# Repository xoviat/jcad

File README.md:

# JCAD: A JLCPCB Manufacturing File Generator for KiCad

JCAD is a program to generate manufacturing files for JLCPCB directly from a `.kicad_pcb` file.
In contrast to other approaches, JCAD does not integrate with KiCad directly or require modification
of schematic or PCB design files in order to generate outputs. Instead, JCAD relies on a consistent
component naming scheme that allows the program to generate manufacturing files from a PCB file in
seconds once the configuration has been established.

## How JCAD works

JCAD associates each combination of designator, footprint, and value on a KiCad PCB with a specific
JLCPCB part. JCAD uses KiCad's new builtin command line client to extract data from the KiCad files
then matches this data with its internal database to prepare manufacturing files.

To reduce designer configuration, JCAD relies on a strict naming scheme for basic parts, and a more
flexible naming scheme for extended parts:

- Basic capacitors, inductors, and resistors must be named unitless
    * Example: 10u, 10k, 10p
- Numerical component values must be equal to or greater than 1, and must use decimal format
    * Example: 10.1k, 10.5p
- Designators must be labeled as follows:
    * Inductors, ferrite beads, and common-mode chokes must be labeled with the L designator
    * Transformers must be labeled with the T designator
    * Crystals must be labeled with the Y designator
- Extended components, including capacitors, inductors, and resistors, and all other basic components must be given the manufacturer name

## Generating Manufacturing Files

The core of JCAD is the `jcad generate` command. The command, when executed in the directory of a `.kicad_pcb` file, reads the PCB and generates three files:
- A `.zip` file containing the gerbers that can uploaded on the order page
- The `-cpl.csv` and `-BOM.csv` files that can be uploaded on the assembly page

If only basic parts are used, and if naming conventions are adhered to, then no
additional user input should be required. If extended components are used, then
the user will need to provide the LCSC part number for each extended component
not already associated. Again, because the association is global, these
associations only need to be provided once.

JCAD doesn't specify component rotations because these are corrected during DFM
review. The silkscreen should always allow the reviewer to correct component
rotations and the rotations given in the CPL file should onlybe seen as 
advisory.

## Configuring KiCad

A major advantage of JCAD is that to work with it, KiCad requires little or no
configuration beyond what is usually required. However, it's a good idea to
create custom symbol and footprint libraries to contain the parts commonly used
when manufacturing boards with JLCPCB. 

For basic resistors, capacitors, and inductors, the standard symbols should
be used and the value should be modified as specified in the naming convention,
rather than creating separate symbols for each value. In all cases, creating a
custom footprint should be a last resort used only when a builtin footprint
is not available.

Basic components should be used where possible and the resistor calculators
given below should be used to recalculate dividers to use values available
in basic parts: 

- https://damien.douxchamps.net/elec/resdiv/
- https://www.qsl.net/in3otd/parallr.html 

## Initial Configuration

JCAD requires a go compiler to build. Once built, `jcad load` must be executed
to load the basic components. Then, JCAD is ready to begin generating files.

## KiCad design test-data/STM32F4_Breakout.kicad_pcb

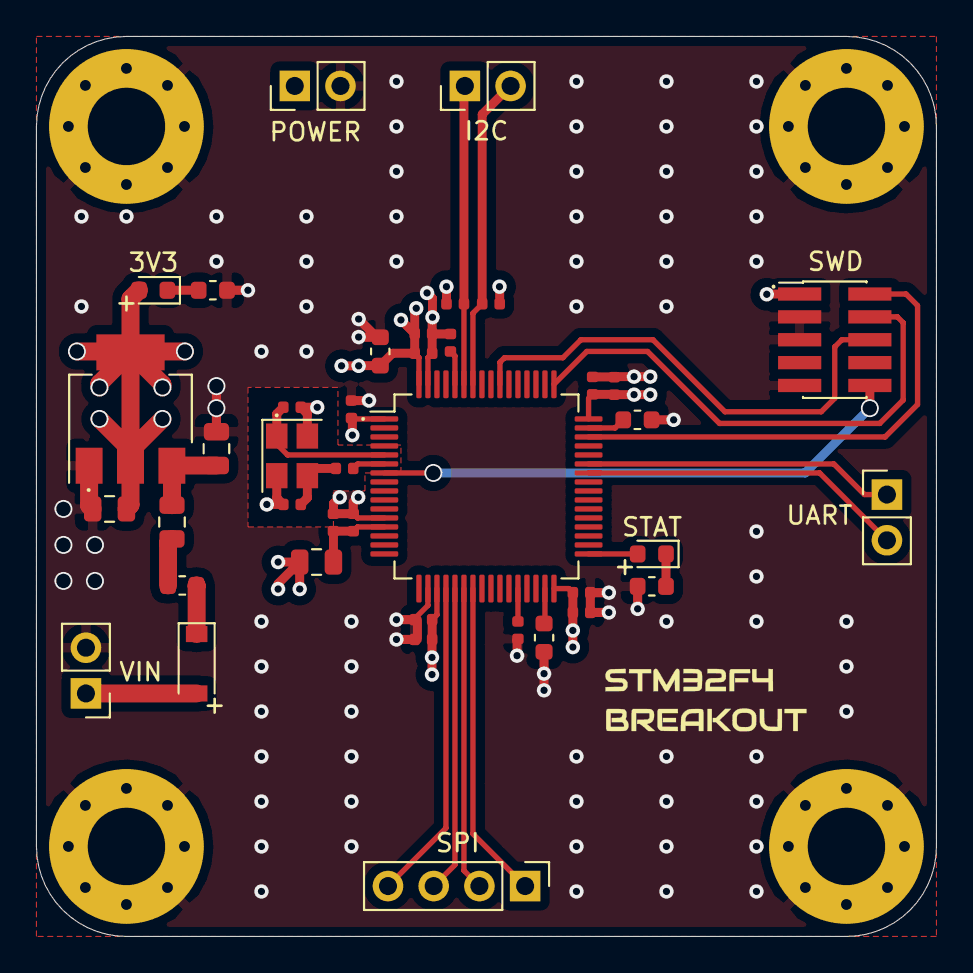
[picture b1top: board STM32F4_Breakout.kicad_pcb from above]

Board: 4 copper layers, 50.0 x 50.0 mm, 44 parts (0 on the bottom side), 29 nets.

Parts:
C1, C2: 10u; C_0805_2012Metric
C3: 10u; C_0603_1608Metric
C4, C5, C6, C7, C8, C9, C10, C11, C12, C13: 100nf; C_0402_1005Metric
C14: 10n; C_0402_1005Metric
C15, C16: 2.2u; C_0603_1608Metric
C17, C18: 12p; C_0402_1005Metric
D1: B5819W; D_SOD-123
D2, D3: Red; LED_0603_1608Metric
F1: 500mA; Fuse_0603_1608Metric
FB1, FB2: 100 @ 100 MHz; L_0805_2012Metric
H1, H2, H3, H4: MountingHole_Pad; MountingHole_4.3mm_M4_Pad_Via
HSE1: 16MHz; Crystal_SMD_3225-4Pin_3.2x2.5mm
J1, J2, J3, J5: Conn_01x02; PinHeader_1x02_P2.54mm_Vertical
J4: Conn_02x05_Odd_Even; PinHeader_2x05_P1.27mm_Vertical_SMD
J6: Conn_01x04; PinHeader_1x04_P2.54mm_Vertical
R1, R7: 2k2; R_0603_1608Metric
R2, R3: 10k; R_0402_1005Metric
R4, R5: 2k2; R_0402_1005Metric
R6: 220; R_0402_1005Metric
U1: AMS1117-3.3; SOT-223-3_TabPin2
U2: STM32F405RGT6; LQFP-64_10x10mm_P0.5mm

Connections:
+3.3VA: C13.1, C14.1, FB2.1, U2.13
+3V3: C2.1, C3.1, C4.1, C5.1, C6.1, C7.1, C8.1, C9.1, C10.1, C11.1, C12.1, D2.2, FB2.2, J3.1, J4.1, R4.1, R5.1, U1.2, U2.1, U2.19, U2.32, U2.48, U2.64
BOOT0: R2.1, U2.60
BOOT1: R3.1, U2.28
GND: C1.2, C2.2, C3.2, C4.2, C5.2, C6.2, C7.2, C8.2, C9.2, C10.2, C11.2, C12.2, C13.2, C14.2, C15.2, C16.2, C17.2, C18.2, H1.1, H2.1, H3.1, H4.1, HSE1.2, HSE1.4, J1.2, J3.2, J4.3, J4.5, J4.9, R1.2, R2.2, R3.2, R7.2, U1.1, U2.12, U2.18, U2.63
HSE_IN: C17.1, HSE1.1, U2.5
HSE_OUT: R6.1, U2.6
I2C1_SCL: J5.2, R4.2, U2.58
I2C1_SDA: J5.1, R5.2, U2.59
NRST: J4.10, U2.7
unnamed: C1.1, FB1.1, U1.3
unnamed: C15.1, U2.31
unnamed: C16.1, U2.47
unnamed: C18.1, HSE1.3, R6.2
unnamed: D1.1, F1.1
unnamed: D2.1, R1.1
unnamed: D3.1, R7.1
unnamed: D3.2, U2.33
unnamed: F1.2, FB1.2
SPI1_CS: J6.4, U2.20
SPI1_MISO: J6.2, U2.22
SPI1_MOSI: J6.1, U2.23
SPI1_SCK: J6.3, U2.21
SWCLK: J4.4, U2.49
SWDIO: J4.2, U2.46
SWO: J4.6, U2.55
USART1_RX: J2.1, U2.43
USART1_TX: J2.2, U2.42
VCC: D1.2, J1.1

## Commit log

2020-10-03 Lay-out project vision
2020-10-03 impl. basic project structure
2020-10-03 add component database
2020-10-03 generate cpl file
2020-10-04 generate gerbers
2020-10-04 fix gerber naming
2020-10-04 implement import library
2020-10-04 schematic: impl. target values
2020-10-04 implement find maching components
2020-10-04 implement schematic parsing
2020-10-04 draft generate files from cpl output
2020-10-04 impl. draft generate command
2020-10-04 update strategy
2020-10-04 abandon GUI plan
2020-10-04 get basic scheme working
2020-10-04 resolve small bugs
2020-10-05 cleanup cpl processing
2020-10-05 further generate cleanup
2020-10-05 commit results
2020-10-05 python: write rows with csv module
2020-10-05 cleanup; exclude nonviable components
2020-10-05 re-generate files
2020-10-05 add archiver
2020-10-05 store component rotation in database
2020-10-06 add suggestion functionality and cleanup
2020-10-06 rework component library api
2020-10-06 implement draft indexing routine
2020-10-06 generate suggestions
2020-10-10 add eagle library parsing
2020-10-11 implement category listing
2020-10-11 misc cleanup
2020-10-11 generate the capacitor libray
2020-10-11 misc. fixees and cleanups
    factor out variables
    fix import and generation
2020-10-11 misc. library fixes
2020-10-11 impl. draft import-library command
2020-10-11 add get package/symbol functions
2020-10-11 implement library generation without sourcer
2020-10-12 add value for inductors
2020-10-12 print packages and symbols imported
2020-10-16 fix incorrect prompt
2020-10-16 add ability to re-associate components
2020-10-16 integrate set-rotation into generate
2020-10-16 misc. cleanup
2020-10-20 store components to skip
2020-10-27 check for existance of file before proceeding
2020-11-09 clean gerber directory
2020-11-18 consolidate symbol association
2020-11-18 rename commands
2020-11-18 create extended library by default
2020-11-18 open database once
2020-11-18 small comment fix
2020-11-24 cleanup case
2020-11-24 add svg data and prelim. code
2020-11-26 minor svg cleanup
2020-11-28 consolidate import commands
2020-11-28 eliminate need for second pass
2020-11-29 add option to rename symbol
2020-12-01 allow tilde prefix on home dir
2020-12-07 skip solder jumpers
2020-12-09 skip din rail adapter
2021-01-13 add non-assembleable components
2022-07-03 update for kicad 6
2022-07-03 improve doc
2022-07-03 cleanup bom handling
2022-07-04 improve clarity and fix C0 bug
2022-07-04 simplify key scheme
2022-07-04 fix invalid pattern
2022-07-04 add todo to import
2022-07-04 cleanup data structure
2022-07-09 create new assocationmap abstraction
2022-07-09 add csv library support
2022-07-09 index common components on import
2022-07-09 implement suggestions for basic components
2022-07-10 - add normalizevalue - fix bug in assocationmap
2022-07-10 update libraries
2022-07-10 filter results by pkg assocation
2022-09-01 generate cleaner cpl files
2022-10-02 update copyright
2022-10-02 - validate paths in normalize function - add draft export command
2022-10-02 improve scripts location detection
2022-10-02 add PCB design rules
2022-10-08 remove eagle functionality
2022-10-08 reorganize database import
2022-10-08 impl. draft export component associations
2022-10-16 export associations to excel file
2022-10-16 add draft import assocations
2022-10-25 impl. import associations
2022-11-06 update pcb design rules
2023-02-27 add missing components to db
2023-03-04 use new builtin kicad-cli
2023-03-05 cleanup and use pkg from pcb, not db
2023-03-05 update readme; remove rotation logic
2023-03-06 Add draft jlc component api
2023-03-07 impl. selectComponentList draft fn
2023-03-11 jlc: fetch initial component list
2023-03-12 fully implement initial JLC api
2023-03-12 impl. search suggestions
2023-03-12 improve search results
2023-03-12 autoload components not already in db
2023-03-12 remove unused functionality
2023-03-12 update dependencies
2023-03-12 update README and fix error
2023-03-25 remove old test data
2023-04-01 ci: add cfg
2023-04-01 ci: add upload release assets
2023-04-01 ci: add release-tag option
2023-04-01 ci: fix push triggers
2023-04-01 ci: add new releases action
2023-04-02 consolidate import/export into new edit cmd
2023-04-30 cmd/edit: fix export
2024-05-04 update kicad version
2024-05-04 autodetect kicad version and update deps
2024-07-04 polish edit command
2024-07-14 screen for abnormal comments
2024-08-17 jlc: update api base url
2026-02-24 allow generating connectors
2026-02-24 ci: update version
2026-03-21 impl. in-place lib editing; update deps
